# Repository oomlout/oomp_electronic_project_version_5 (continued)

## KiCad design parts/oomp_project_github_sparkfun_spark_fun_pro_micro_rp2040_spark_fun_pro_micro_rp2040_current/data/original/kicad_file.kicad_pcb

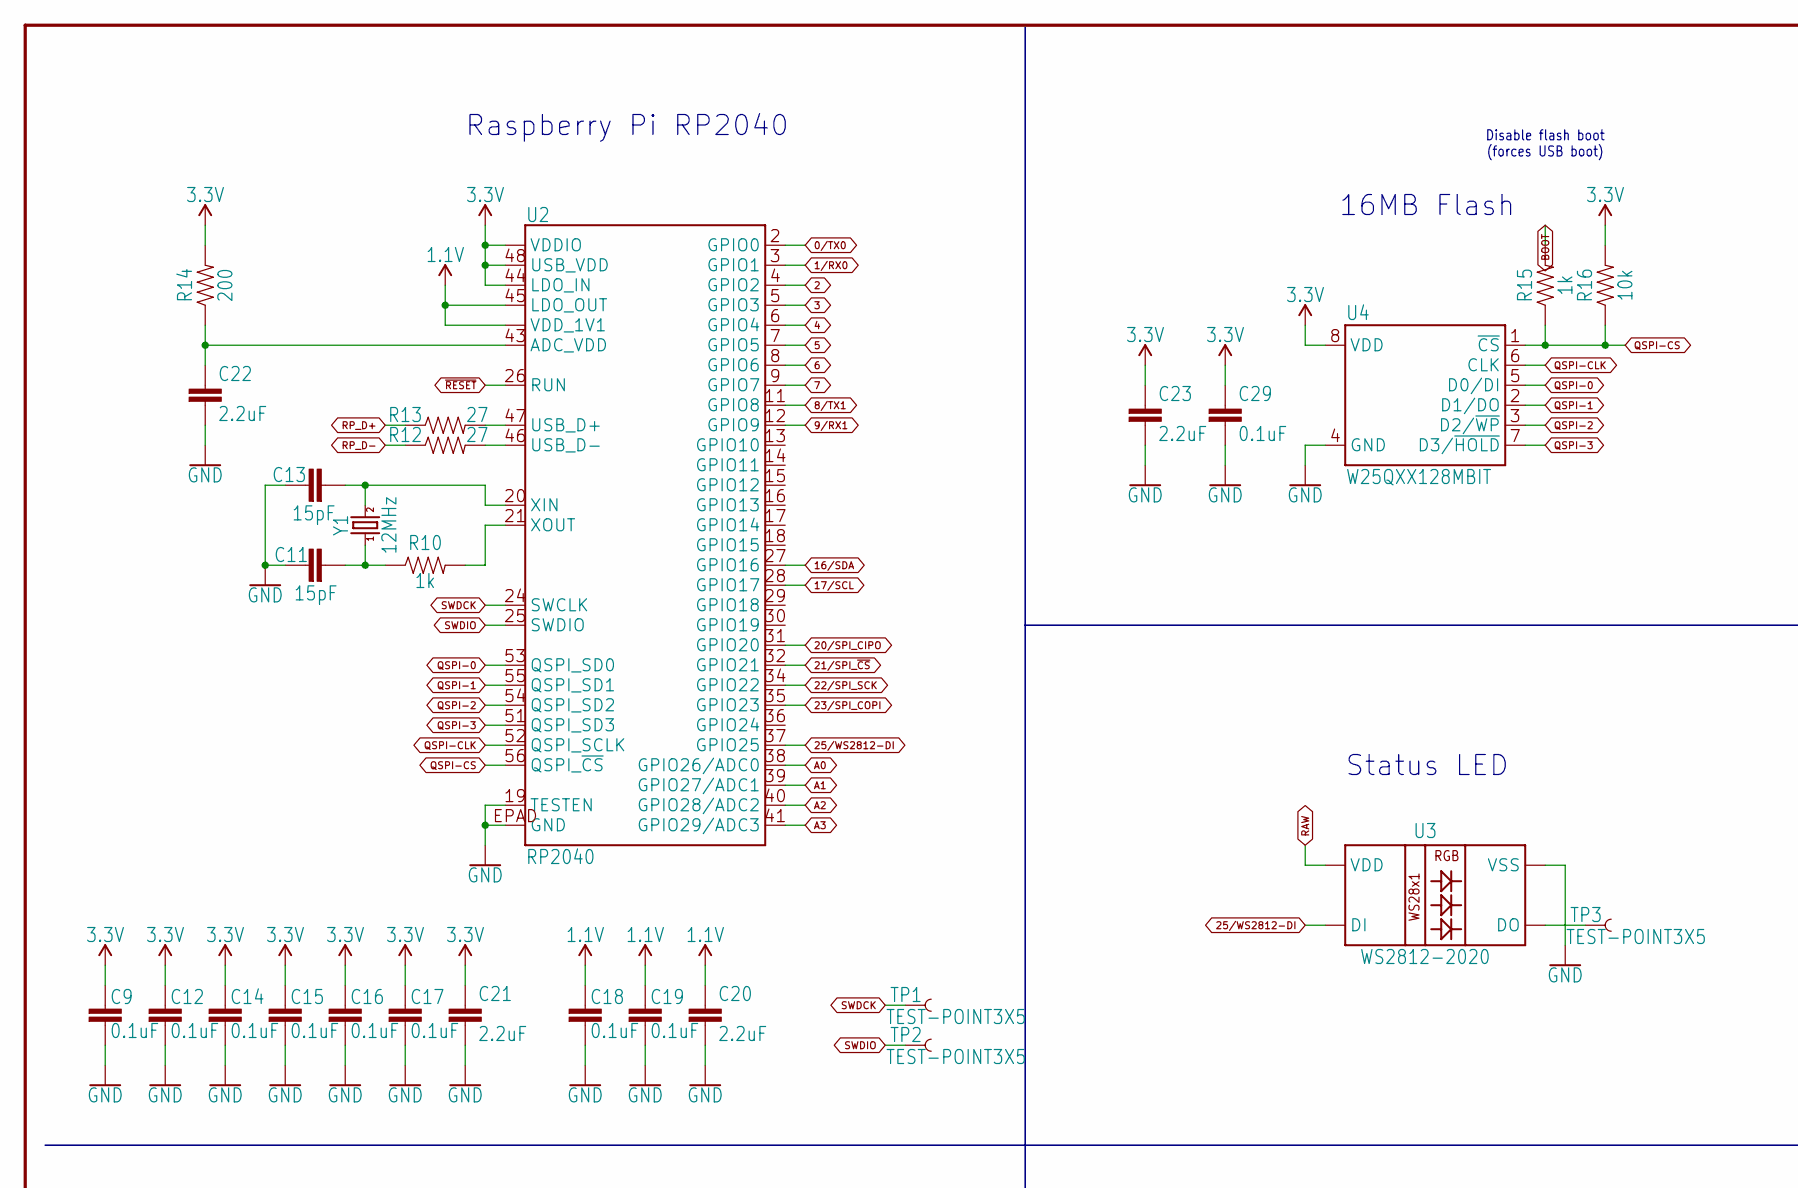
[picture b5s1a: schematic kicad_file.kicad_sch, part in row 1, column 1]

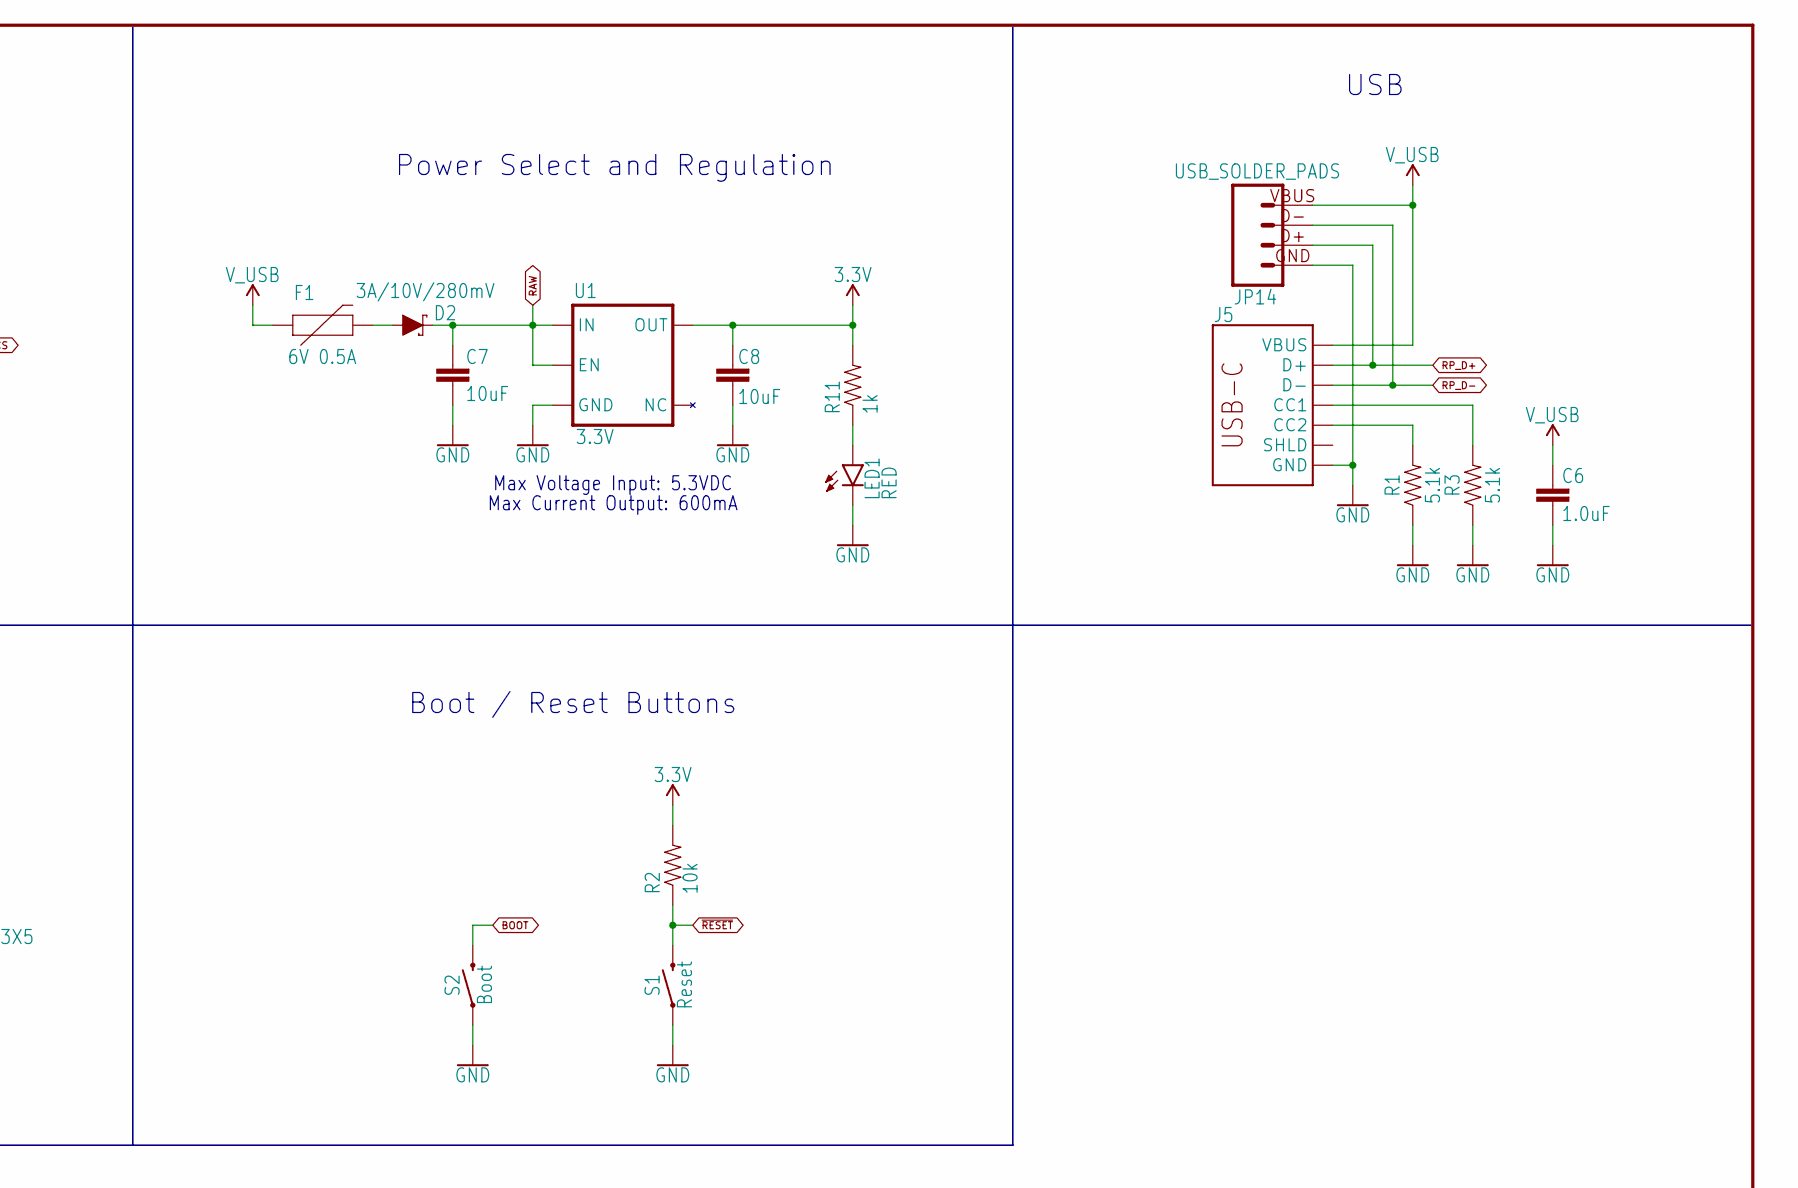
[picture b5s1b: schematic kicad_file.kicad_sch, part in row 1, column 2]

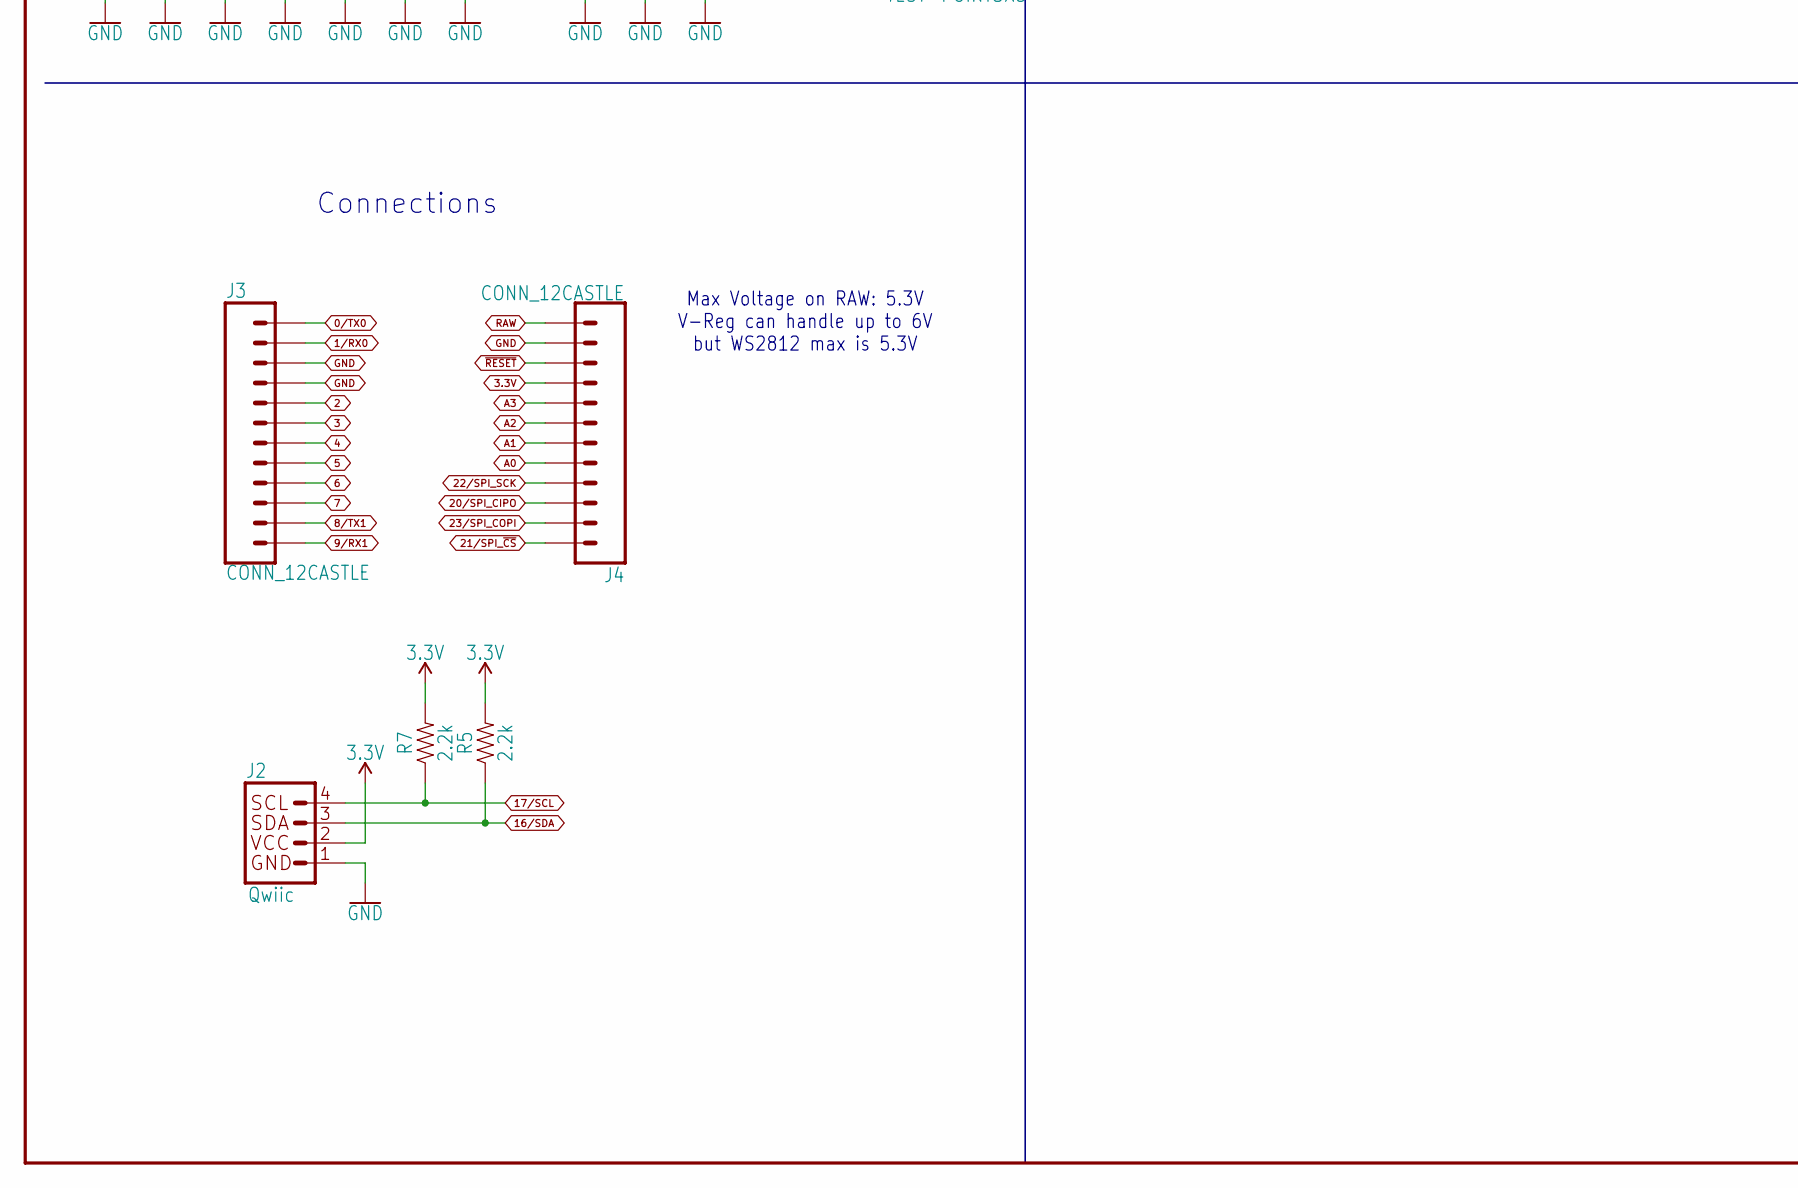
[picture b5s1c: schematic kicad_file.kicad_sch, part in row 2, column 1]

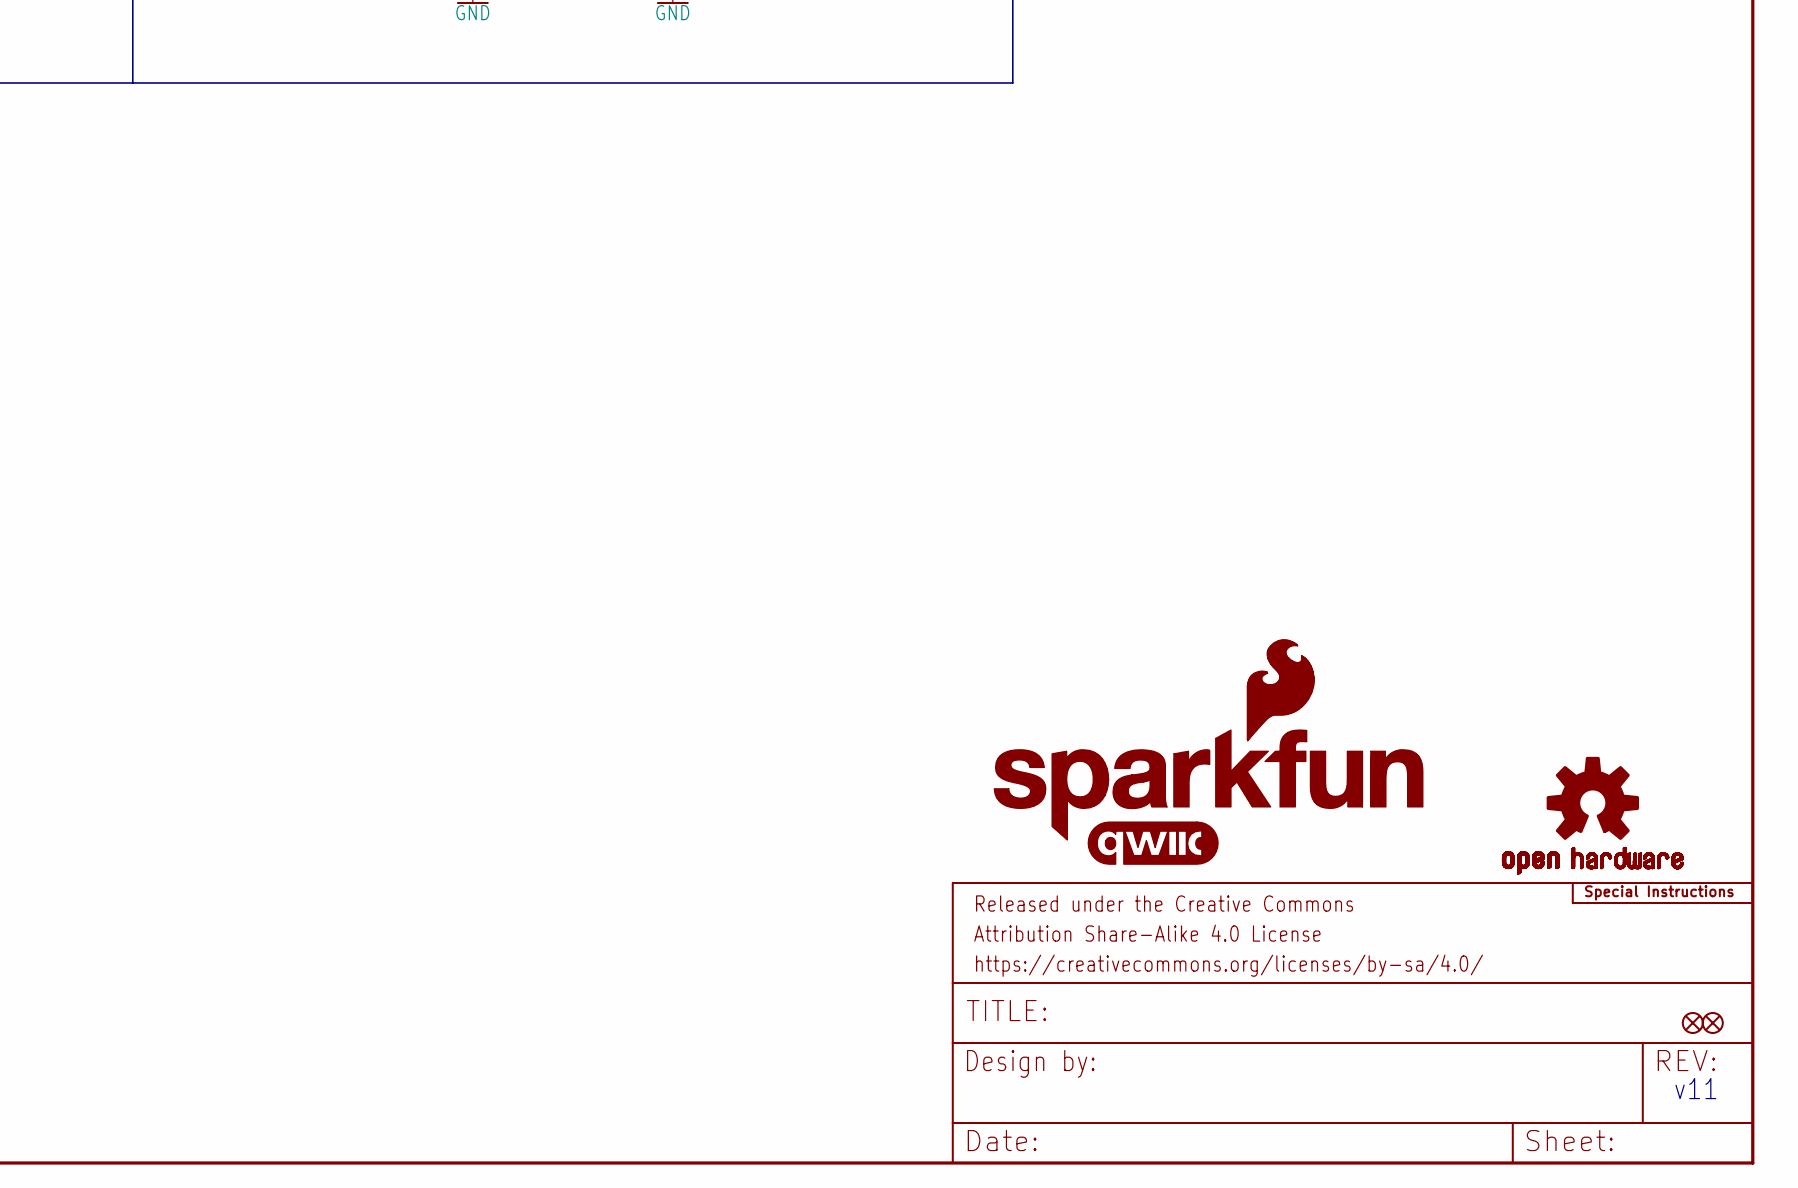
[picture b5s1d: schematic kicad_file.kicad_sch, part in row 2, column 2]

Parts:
C6: 1.0uF; 0402-TIGHT
C7, C8: 10uF; 0402-TIGHT
C9, C12, C14, C15, C16, C17, C18, C19, C29: 0.1uF; 0402-TIGHT
C11, C13: 15pF; 0402-TIGHT
C20, C21, C22, C23: 2.2uF; 0402-TIGHT
D2: 3A/10V/280mV; SOD-323
F1: 6V 0.5A; 0805
FRAME2: FRAME-LEDGER; CREATIVE_COMMONS
J2: Qwiic; JST04_1MM_RA
J3, J4: CONN_12CASTLE; 1X12_CASTELLATED
J5: USB Female Type C Connector; USB-C-16P_4LAYER-PADS
JP1, JP2: FIDUCIAL1X2; FIDUCIAL-1X2
JP14: USB_SOLDER_PADS; USB-SOLDER-PADS
LED1: RED; LED-0603
LOGO1: SFE_LOGO_NAME_FLAME.1_INCH; SFE_LOGO_NAME_FLAME_.1
LOGO3: QWIIC_LOGO_6MM; QWIIC_6MM
LOGO4: SFE_LOGO_FLAME.1_INCH; SFE_LOGO_FLAME_.1
LOGO5: SPECIAL_INSTRUCTIONS-ORDERING; ORDERING_INSTRUCTIONS
R1, R3: 5.1k; 0402-TIGHT
R2, R16: 10k; 0402-TIGHT
R5, R7: 2.2k; 0402-TIGHT
R10, R11, R15: 1k; 0402-TIGHT
R12, R13: 27; 0402-TIGHT
R14: 200; 0402-TIGHT
S1: Reset; TACTILE_SWITCH_SMD_4.6X2.8MM
S2: Boot; TACTILE_SWITCH_SMD_4.6X2.8MM
TP1, TP2, TP3: TEST-POINT3X5; PAD.03X.05
U1: 3.3V; SOT23-5
U2: RP2040; QFN-56
U3: WS2812-2020
U4: W25QXX128MBIT; WSON-8-6X5-SKINNY_CENTERPAD
U$3: OSHW-LOGOMINI; OSHW-LOGO-MINI
Y1: 12MHz; CRYSTAL-SMD-2X2.5MM

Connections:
0/TX0: J3.12, J3.12B (12), U2.2 (GPIO0)
1.1V: C18.1, C19.1, C20.1, U2.23 (VDD_1V1), U2.45 (LDO_OUT), U2.50 (VDD_1V1)
1/RX0: J3.11, J3.11B (11), U2.3 (GPIO1)
2: J3.8, J3.8B (8), U2.4 (GPIO2)
3: J3.7, J3.7B (7), U2.5 (GPIO3)
3.3V: C8.2, C9.1, C12.1, C14.1, C15.1, C16.1, C17.1, C21.1, C23.1, C29.1, J2.2, J4.4, J4.4B (4), R2.2, R5.2, R7.2, R11.2, R14.2, R16.2, U1.5 (OUT), U2.1 (VDDIO), U2.10 (VDDIO), U2.22 (VDDIO), U2.33 (VDDIO), U2.42 (VDDIO), U2.44 (LDO_IN), U2.48 (USB_VDD), U2.49 (VDDIO), U4.8 (VDD)
4: J3.6, J3.6B (6), U2.6 (GPIO4)
5: J3.5, J3.5B (5), U2.7 (GPIO5)
6: J3.4, J3.4B (4), U2.8 (GPIO6)
7: J3.3, J3.3B (3), U2.9 (GPIO7)
8/TX1: J3.2, J3.2B (2), U2.11 (GPIO8)
9/RX1: J3.1, J3.1B (1), U2.12 (GPIO9)
16/SDA: J2.3, R5.1, U2.27 (GPIO16)
17/SCL: J2.4, R7.1, U2.28 (GPIO17)
20/SPI_CIPO: J4.10, J4.10B (10), U2.31 (GPIO20)
21/SPI_~CS: J4.12, J4.12B (12), U2.32 (GPIO21)
22/SPI_SCK: J4.9, J4.9B (9), U2.34 (GPIO22)
23/SPI_COPI: J4.11, J4.11B (11), U2.35 (GPIO23)
25/WS2812-DI: U2.37 (GPIO25), U3.3 (DI)
A0: J4.8, J4.8B (8), U2.38 (GPIO26/ADC0)
A1: J4.7, J4.7B (7), U2.39 (GPIO27/ADC1)
A2: J4.6, J4.6B (6), U2.40 (GPIO28/ADC2)
A3: J4.5, J4.5B (5), U2.41 (GPIO29/ADC3)
ADC_VDD: C22.1, R14.1, U2.43 (ADC_VDD)
BOOT: R15.2, S2.3 (2), S2.4 (2)
GND: C6.1, C7.1, C8.1, C9.2, C11.1, C12.2, C13.1, C14.2, C15.2, C16.2, C17.2, C18.2, C19.2, C20.2, C21.2, C22.2, C23.2, C29.2, J2.1, J3.9, J3.9B (9), J3.10, J3.10B (10), J4.2, J4.2B (2), J5.GND, J5.GND2 (GND), JP14.GND (4), LED1.C, R1.1, R3.1, S1.1, S1.2 (1), S2.1, S2.2 (1), U1.2 (GND), U2.19 (TESTEN), U2.EPAD (GND), U3.2 (VSS), U4.4 (GND)
unnamed: TP3.P$1, U3.1 (DO)
unnamed: J5.A5 (CC1), R3.2
unnamed: J5.B5 (CC2), R1.2
unnamed: LED1.A, R11.1
QSPI-0: U2.53 (QSPI_SD0), U4.5 (D0/DI)
QSPI-1: U2.55 (QSPI_SD1), U4.2 (D1/DO)
QSPI-2: U2.54 (QSPI_SD2), U4.3 (D2/~WP)
QSPI-3: U2.51 (QSPI_SD3), U4.7 (D3/~HOLD)
QSPI-CLK: U2.52 (QSPI_SCLK), U4.6 (CLK)
QSPI-CS: R15.1, R16.1, U2.56 (QSPI_~CS), U4.1 (~CS)
RAW: C7.2, D2.C, J4.1, J4.1B (1), U1.1 (IN), U1.3 (EN), U3.4 (VDD)
RP_D1+: R13.2, U2.47 (USB_D+)
RP_D1-: R12.2, U2.46 (USB_D-)
RP_D+: J5.A6 (D+), J5.B6 (D+), JP14.D+ (3), R13.1
RP_D-: J5.A7 (D-), J5.B7 (D-), JP14.D- (2), R12.1
SWDCK: TP1.P$1, U2.24 (SWCLK)
SWDIO: TP2.P$1, U2.25 (SWDIO)
USB_RAW: D2.A, F1.2
V_USB: C6.2, F1.1, J5.VBUS1 (VBUS), J5.VBUS2 (VBUS), JP14.VBUS (1)
X1A: R10.2, U2.21 (XOUT)
X1B: C11.2, R10.1, Y1.P1 (1)
X2: C13.2, U2.20 (XIN), Y1.P3 (2)
~RESET: J4.3, J4.3B (3), R2.1, S1.3 (2), S1.4 (2), U2.26 (RUN)

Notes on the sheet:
Disable flash boot (forces USB boot)
Max Voltage on RAW: 5.3V V-Reg can handle up to 6V but WS2812 max is 5.3V
Boot / Reset Buttons
Power Select and Regulation
16MB Flash
Status LED
v11
USB
Raspberry Pi RP2040
Max Voltage Input: 5.3VDC
Connections
Max Current Output: 600mA

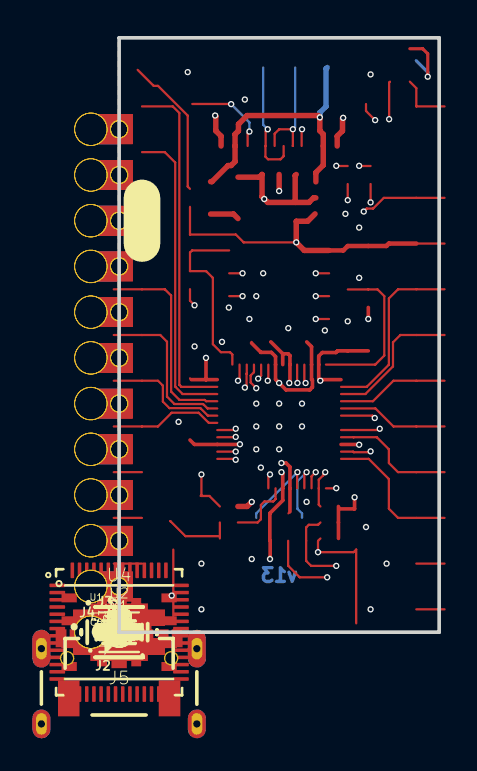
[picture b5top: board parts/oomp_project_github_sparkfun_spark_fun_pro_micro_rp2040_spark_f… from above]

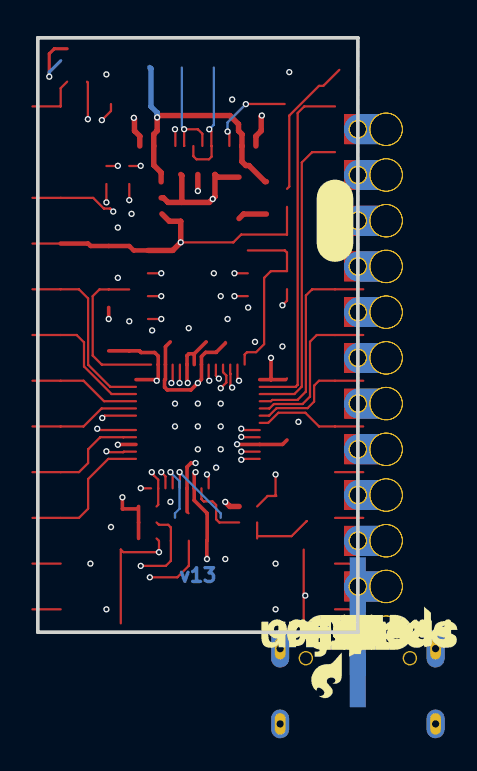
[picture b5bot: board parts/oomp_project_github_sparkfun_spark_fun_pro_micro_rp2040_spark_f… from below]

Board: 4 copper layers, 17.8 x 33.0 mm, 109 parts (39 on the bottom side), 49 nets.

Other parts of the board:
U$1, U$11: A00
U$2: GND_0
U$4: PRO_MICRO0
U$5: #0
U$6: 70
U$7: 81
U$8: 92
U$9, U$64: CI4
U$10, U$67: SCK3
U$12, U$20: A10
U$13, U$33: A21
U$14, U$39: A32
U$15, U$22, U$74: GND2
U$16: 3V3_0
U$17: RAW0
U$18: C0
U$19, U$76: TX0
U$21, U$75: RX1
U$23, U$53: 20
U$24, U$54: 31
U$25, U$55: 42
U$26, U$56: 53
U$27, U$57: 64
U$28: D#1
U$29: D#2
U$30: G0
U$31: V3
U$32: 210
U$34: #RST#0
U$35: D1
U$36: B0
U$37: R0
U$38: RP20401
U$40: DO0
U$66: CO5
U$68: #RST#1
U$69: 3V30
U$73: PWR0

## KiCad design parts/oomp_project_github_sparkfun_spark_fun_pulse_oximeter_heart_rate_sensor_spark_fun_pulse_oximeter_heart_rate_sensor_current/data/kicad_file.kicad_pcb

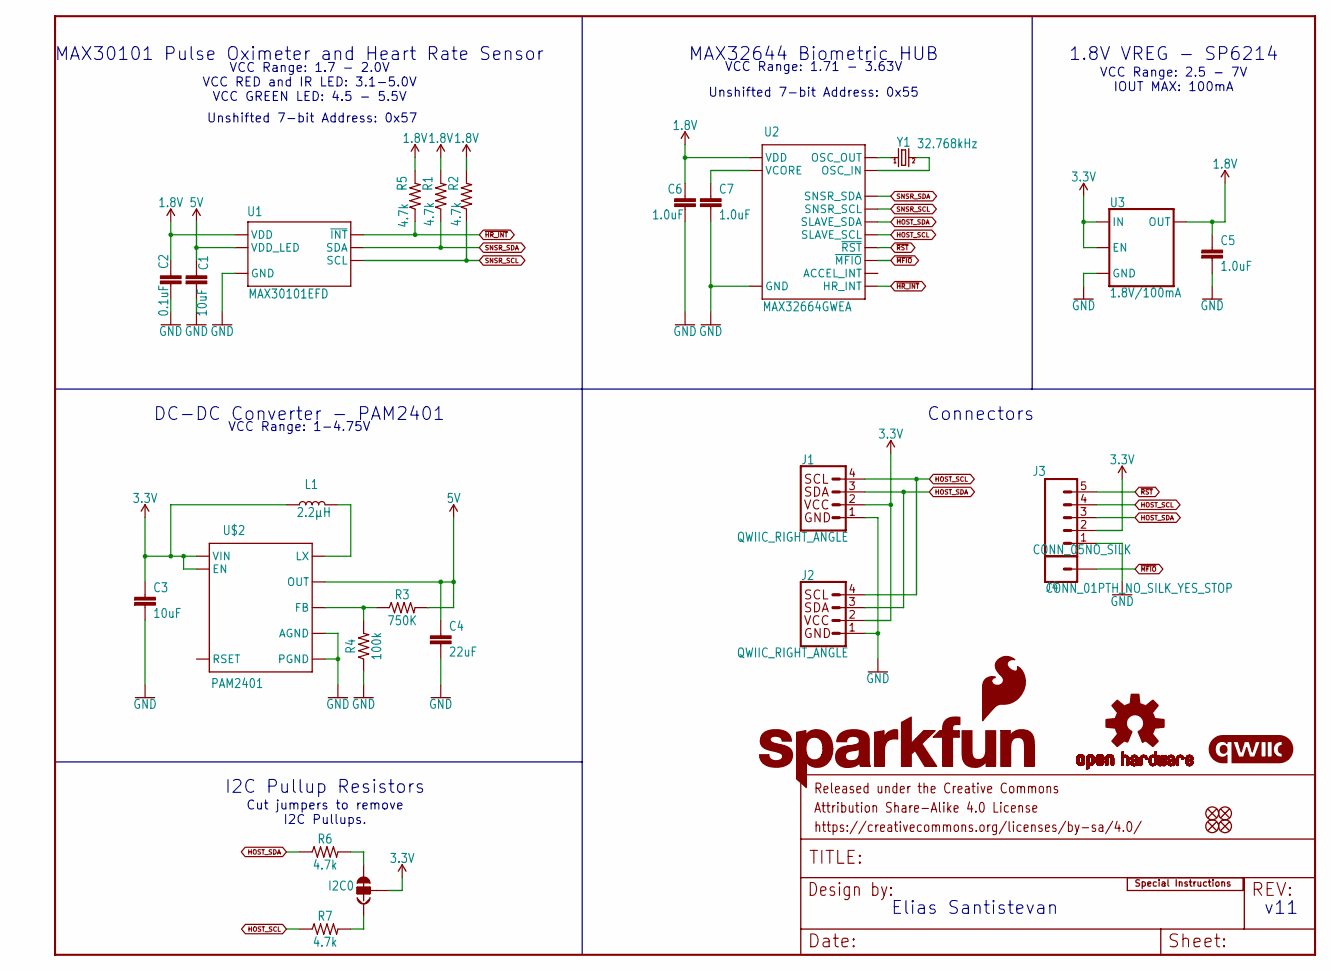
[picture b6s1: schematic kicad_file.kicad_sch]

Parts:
C1, C3: 10uF; 0603
C2: 0.1uF; 0402-TIGHT
C4: 22uF; 0805
C5: 1.0uF; 0603
C6, C7: 1.0uF; 0402-TIGHT
FD1, FD2, FD3, FD4: FIDUCIALUFIDUCIAL; FIDUCIAL-MICRO
FRAME1: FRAME-LETTER; CREATIVE_COMMONS
I2C0: JUMPER-SMT_3_2-NC_TRACE_SILK; SMT-JUMPER_3_2-NC_TRACE_SILK
J1, J2: QWIIC_RIGHT_ANGLE; JST04_1MM_RA
J3: CONN_05NO_SILK; 1X05_NO_SILK
J4: CONN_01PTH_NO_SILK_YES_STOP; 1X01_NO_SILK
L1: 2.2μH; 0806
LOGO1: SFE_LOGO_FLAME.1_INCH; SFE_LOGO_FLAME_.1
LOGO2: OSHW-LOGOMINI; OSHW-LOGO-MINI
LOGO3: SFE_LOGO_NAME.1_INCH; SFE_LOGO_NAME_.1
LOGO4: SPECIAL_INSTRUCTIONS-ORDERING; ORDERING_INSTRUCTIONS
LOGO5: QWIIC_LOGO_4MM; QWIIC_4MM
R1, R2, R5, R6, R7: 4.7k; 0603
R3: 750K; 0603
R4: 100k; 0402-TIGHT
U1: MAX30101EFD; 14_PIN_OESIP
U2: MAX32664GWEA; 16_PIN_WLP
U3: 1.8V/100mA; SC70
U$2: PAM2401; MSOP8
Y1: 32.768kHz; CRYSTAL-SMD-3.2X1.5MM

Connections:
1.8V: C2.1, C5.1, C6.1, R1.2, R2.2, R5.2, U1.P11 (VDD), U2.3 (VDD), U3.5 (OUT)
3.3V: C3.1, I2C0.2, J1.2, J2.2, J3.2, L1.1, U3.1 (IN), U3.3 (EN), U$2.2 (EN), U$2.3 (VIN)
5V: C1.1, C4.1, R3.2, U1.P9 (VDD_LED), U1.P10 (VDD_LED), U$2.7 (OUT)
GND: C1.2, C2.2, C3.2, C4.2, C5.2, C6.2, C7.2, J1.1, J2.1, J3.1, R4.1, U1.P4 (GND), U1.P12 (GND), U2.13 (GND), U3.2 (GND), U$2.4 (AGND), U$2.8 (PGND)
HOST_SCL: J1.4, J2.4, J3.4, R7.1, U2.10 (SLAVE_SCL)
HOST_SDA: J1.3, J2.3, J3.3, R6.1, U2.9 (SLAVE_SDA)
unnamed: C7.1, U2.4 (VCORE)
unnamed: R3.1, R4.2, U$2.5 (FB)
unnamed: L1.2, U$2.1 (LX)
unnamed: I2C0.3, R6.2
unnamed: I2C0.1, R7.2
unnamed: U2.1 (OSC_OUT), Y1.P$1 (1)
unnamed: U2.2 (OSC_IN), Y1.P$2 (2)
SNSR_SCL: R2.1, U1.P2 (SCL), U2.5 (SNSR_SCL)
SNSR_SDA: R1.1, U1.P3 (SDA), U2.14 (SNSR_SDA)
~HR_INT: R5.1, U1.P13 (~INT), U2.6 (HR_INT)
~MFIO: J4.1, U2.16 (~MFIO)
~RST: J3.5, U2.12 (~RST)

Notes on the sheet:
Connectors
MAX30101 Pulse Oximeter and Heart Rate Sensor
I2C Pullup Resistors
Cut jumpers to remove I2C Pullups.
Unshifted 7-bit Address: 0x57
v11
MAX32644 Biometric HUB
VCC Range: 1-4.75V
VCC Range: 1.7 - 2.0V VCC RED and IR LED: 3.1-5.0V VCC GREEN LED: 4.5 - 5.5V
DC-DC Converter - PAM2401
1.8V VREG - SP6214
Unshifted 7-bit Address: 0x55
VCC Range: 1.71 - 3.63V
Elias Santistevan
VCC Range: 2.5 - 7V IOUT MAX: 100mA

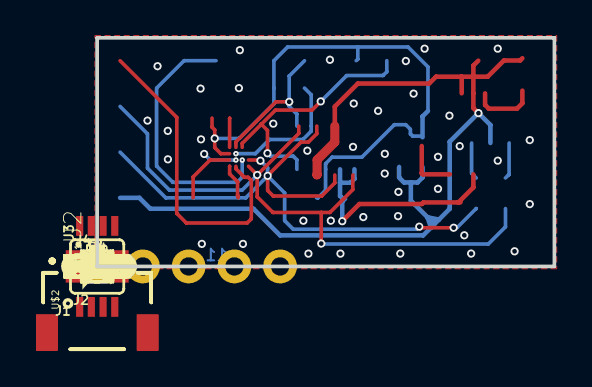
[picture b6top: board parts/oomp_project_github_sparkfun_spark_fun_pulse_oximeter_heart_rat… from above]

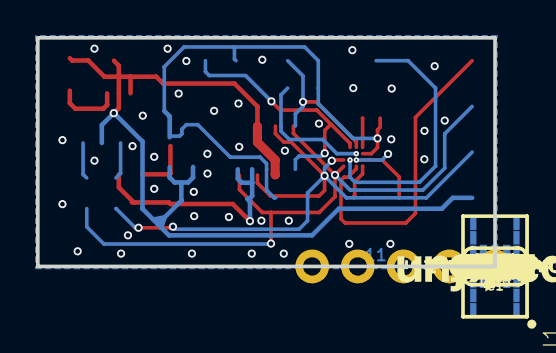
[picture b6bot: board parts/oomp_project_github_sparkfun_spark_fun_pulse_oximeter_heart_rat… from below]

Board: 2 copper layers, 25.4 x 12.7 mm, 50 parts (24 on the bottom side), 18 nets.

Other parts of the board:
U$1: #I2C#1348
U$3, U$5: #GND#0
U$4: #SCL#7
U$6, U$12: #RST#32
U$7: 3V338
U$8: #SDA#10
U$9: #3V3#1
U$10: #SDA#9
U$11: #SCL#9
U$13: ##MFIO##12
U$17: PULSE35
U$20: OXIMETER_AND36
U$21: HEART_RATE_MONITOR37

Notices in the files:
parts/oomp_project_github_sparkfun_spark_fun_nano_beacon_board_in100_spark_fun_nano_beacon_board_in100_current/data/original/kicad_file.kicad_sch:
Released under the Creative Commons
https://creativecommons.org/licenses/by-sa/4.0
parts and their libraries:
Released under the Creative Commons Attribution Share-Alike 4.0 License
